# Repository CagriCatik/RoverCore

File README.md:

# RoverCore

Modulare VCU-Trägerplatine (Rev 1) für einen RC-Rover: steckbares
ESP32-S3-DevKitC-1, IMU (Adafruit 4438), OLED (Adafruit 326), geregelte
Servoschiene, 5-V-Logikversorgung, LED-, Empfänger- und UART-Ausgänge.
KiCad 10.0.7, 4 Lagen, 160 × 85 mm (Variante B, vier M3-Eckbohrungen).

**Stand 2026-11-18: Variante B umgesetzt, DRAFT-Paket A3 (NO-GO). Fertigung gestoppt bis zum Fahrzeugabgleich.**
ERC, DRC und Schaltplan-Parität bestehen im lokalen Lauf. Der
JLCPCB-Regelsatz im DRC prüft Kupfer, Bohrungen und Texte, aber keine
Linienbreiten im Bestückungsdruck (bekannte Abweichung, siehe unten). Das ist ein Werkzeugergebnis; elektrische, thermische und
fertigungstechnische Freigabe stehen aus. Nächster Schritt ist der
prüfbare Prototyp nach dem [Inbetriebnahmeplan](docs/bringup.md).

## Ansichten

Review-Ansichten (`hardware/scripts/render_populated_review.py`): Bauteile mit
KiCad-Bibliotheksmodell erscheinen normal. J102/J103 zeigen das Molex-Herstellermodell
(projektlokal, nicht in Git). J101 XT30, BZ101, Q101, Q401/Q402 und D601–D604, D606–D608 zeigen **selbst erzeugte,
vereinfachte Gehäusemodelle nach den Maßzeichnungen der Hersteller** – keine heruntergeladenen Herstellermodelle
(`hardware/scripts/make_package_models.py`, MIT, als STEP und VRML; Maße und Quellen in
`hardware/libraries/3d-models/models.csv`; geschätzt bzw. vereinfacht: XT30-Höhe, Anschlussform BZ101).
**Blau** sind Hüllkörper der gesteckten Module (DevKit, OLED, IMU), Höhen geschätzt. Hüllkörper und eigene Modelle
sind keine verlässlichen mechanischen Modelle; die echten Teile entscheiden beim Passungstest.
Status je Position in `qa/generated/populated/model_status.csv`, Bericht 3g, 3l, 3m.

| Mit Modulen | Ohne Module (Buchsenleisten) |
|---|---|
|  |  |
|  |  |
|  |  |
|  |  |

Befestigung Variante B ([Bericht](docs/vcu/rev1-befestigung-vorschlag.md)): vier M3-Bohrungen, NPTH 3,2 mm,
(4,5 | 4,5), (4,5 | 80,5), (155,5 | 18,0), (155,5 | 80,5); vorläufig bis zum Fahrzeugabgleich; orange in
den 3D-Ansichten = Hüllkörper für Scheibe, Kopf und 10-mm-Abstandshalter.

**Im Browser ansehen:** [drehbares 3D-Modell und interaktive Stückliste (iBOM)](https://cagricatik.github.io/RoverCore/vcu/ansicht/)
(DRAFT A3.1; ohne die Herstellermodelle von J102/J103, siehe dort).

Aus den exportierten Gerber- und Bohrdateien gezeichnet
(`scripts/kit fab preview`), also so, wie der Fertiger sie erhält:

| Oberseite (Gerber) | Unterseite (Gerber, von unten) | Innenlage In1 (GND) |
|---|---|---|
|  |  |  |

## Eckdaten (Auslegung, nicht gemessen)

| Größe | Wert |
|---|---|
| Eingang | 3S-LiPo, 9,0–12,6 V, XT30, Sicherung 15 A, Verpolschutz Q101, TVS D101 |
| Servoschiene | LTC7803, Sollwert 6,8 V (vorläufig, O-19), Auslegung 11,2 A (zwei blockierte Lenkservos), Strommessung INA240A3 an 2 mΩ |
| Logik | TPS54302, +5V 4,74–5,16 V; DevKit über D501 (PMEG4010CEH), +3V3 aus dem DevKit-LDO |
| Freigabe | `SERVO_PWR_EN` und Freigabe-Latch (SW501, Wiederanlaufsperre 9,62–10,40 V) |
| Lagenaufbau | Fertigungsvorgabe 35 / 17,5 / 17,5 / 35 µm, Prepreg 0,1 mm, 1,6 mm, Hülse IPC-6012 Kl. 2 – beim Fertiger zu bestätigen |

## Dokumentation

| Dokument | Inhalt |
|---|---|
| [Erstinbetriebnahme](docs/bringup.md) | Schrittfolge Versorgung, D501, Servostrompfad, Grenzwerte und Abbruchkriterien |
| [Versorgung und Boardwahl](docs/vcu/rev1-versorgung-und-boardwahl.md) | Auslegung aller Versorgungen, Schutz, Wiederanlaufsperre |
| [Pin- und Anschlussplan](docs/vcu/rev1-pin-und-anschlussplan.md) | GPIO-Belegung, Stecker (maschinenlesbar: `hardware/interfaces/pinmap.csv`) |
| [Platzierung, Routing, Fertigung](docs/vcu/rev1-platzierung.md) | Platzierung, Routing K1, Strompfade (3j), Fertigerabgleich und DRAFT-Paket (3k) |
| [Mechanischer Abgleich](docs/vcu/rev1-mechanik-abgleich.md) | Prüfliste am Fahrzeug, 1:1-Vorlage, Auflage unter dem DevKit |
| [Review 2026-11-15](docs/vcu/rev1-review-2026-11-15.md) · [Werkzeuge](docs/vcu/tooling-integration.md) | Schaltplan-Review, lokale Werkzeuge |
| [Engineering-Richtlinien](docs/engineering/README.md) | allgemeine Regeln aus dem Template |

Online: <https://cagricatik.github.io/RoverCore/>

## Offen vor einer Bestellung

- Lagenaufbau und **Mindest**-Hülsendicke 18 µm schriftlich beim Fertiger
  bestellen (JLCPCB nennt nur einen Mittelwert von 18 µm).
- D502 festgelegt (Würth 150060RS75000); LCSC-Nummer und JLCPCB-Bestand prüfen.
- Datenblattfelder (44 Teile), 3D-Modelle (14), Bauteilakten.
- Bestückungsdruck: 1 211 Umrissstriche mit 0,12 mm im exportierten Gerber
  (JLCPCB verlangt 0,15 mm); Entscheidung offen (Bericht 3l).
- **Befestigung Variante B umgesetzt** (Kontur 160 × 85, vier Eckbohrungen); offen ist der
  Abgleich am Fahrzeug mit der 1:1-Vorlage ([Prüfliste](docs/vcu/rev1-mechanik-abgleich.md)) und der
  Stecktest am DevKit (ob die Auflage unter dem DevKit nötig ist). Ergebnisse der Prüfung des Umbaus
  in [rev1-befestigung-vorschlag.md](docs/vcu/rev1-befestigung-vorschlag.md).
- Bohrdateien: `kit export` liefert getrennt `RoverCore-PTH.drl` und
  `RoverCore-NPTH.drl`; beide hochladen und die 10 NPTH-Löcher in der
  Fertiger-Vorschau prüfen (Bericht 3n).
- 3D / STEP: Alle Carrier-Teile haben ein Modell (`models_3d` 0 Funde). Der Board-STEP (`kit export`,
  `mechanical/board.step`) enthält die eigenen Modelle, ist für Gehäusekonstruktion und Kollisionsprüfung aber
  **unvollständig**: Die gesteckten Module DevKit, OLED und IMU fehlen darin (nur ihre Buchsenleisten; die blauen
  Hüllen gibt es nur in den Review-Bildern), und das Molex-Modell J102/J103 fehlt in einem frischen Checkout,
  solange `vendor/` nicht geladen ist. Eigene Modelle sind vereinfacht (XT30-Höhe geschätzt).
- GO-Freigabe nur mit signierter Freigabe (`manufacturing/approval.example.json`)
  und `--authorize`.

## Repository

| Pfad | Inhalt |
| --- | --- |
| `RoverCore.kicad_pro/.kicad_sch/.kicad_pcb/.kicad_dru` | KiCad-Projekt (Hardware-Wahrheit), Fertiger-Regelsatz |
| `hardware/` | Eigene Bibliotheken (`${KIPRJMOD}`), Schnittstellen, Simulation, Board-Skripte |
| `firmware/` | Firmware, BSP und Treiber (optional) |
| `components/` | Bauteilakten, Datenblätter, SPICE-Modelle |
| `manufacturing/` | Freigabe-Checkliste, Freigaben, erzeugte Exporte (nicht versioniert) |
| `docs/` | Anforderungen, Architektur, Schnittstellen, Inbetriebnahme, Berichte |
| `qa/` | Prüfkonfiguration, Reviews, Berichte |

## Befehle

```sh
scripts/kit install                       # einmalig: lokale .venv (kicad-python, numpy, scipy)
scripts/kit doctor                        # Umgebungsdiagnose, nur lesend
scripts/kit verify .                      # ERC, DRC, Parität, Bibliotheken, Metadaten, 3D, BOM
scripts/kit export . --revision A1        # DRAFT-Fertigungspaket (NO-GO)
scripts/kit thermal analyze .             # stationäre Thermik-Schätzung
scripts/kit power paths .                 # Gleichstrom-Pfade im Kupfer (Schätzung), Fälle in current-paths.json
```

Prüfwerkzeuge für Layout und Fertigungspaket (nur lesend, Ergebnisse unter `qa/generated/`):

```sh
scripts/kit fab check . manufacturing/releases/generated/rev-A3-DRAFT     # Paket gegen Board
scripts/kit fab preview . manufacturing/releases/generated/rev-A3-DRAFT   # Gerber-/Bohrbilder
scripts/kit board diff ALT.kicad_pcb RoverCore.kicad_pcb --project .      # Kupfer-/Bauteilvergleich
scripts/kit models fit . BZ101 hardware/libraries/3d-models/project/SameSky_CMT-8540S-SMT_8.5x8.5x4.0mm.step  # 3D-Sitz
scripts/kit mounting print . --washer 7 --body J101 --body U501           # 1:1-Bohrbild (allgemein)
```

Die Lastfälle für `power paths` stehen in
[`hardware/simulations/power/current-paths.json`](hardware/simulations/power/current-paths.json),
alle Ströme und die Hülsendicke mit Quelle in
[`hardware/interfaces/assumptions.json`](hardware/interfaces/assumptions.json). Die früheren Skripte
`current_map.py`, `board_copper_diff.py`, `fab_package_check.py`, `gerber_preview.py` und
`model_fit_check.py` (in älteren Berichtsabschnitten noch genannt) sind durch diese Befehle ersetzt und
nur noch in der Git-Historie (bis `53f6d7f`). Die RoverCore-spezifischen Montagebilder
(`render_mounting_print.py` mit SUPPORT-Zone und Steckrichtungen, `render_mounting_drawing.py`,
`render_mounting_proposal.py`) bleiben in `hardware/scripts`.

Die Werkzeuge sind aus PCB-Project-Template 2.0.0 übernommen; Herkunft,
Lizenz und lokale Änderungen stehen in [`tools/VENDORED.md`](tools/VENDORED.md).
Regeln für automatisierte Änderungen: [`AGENTS.md`](AGENTS.md).

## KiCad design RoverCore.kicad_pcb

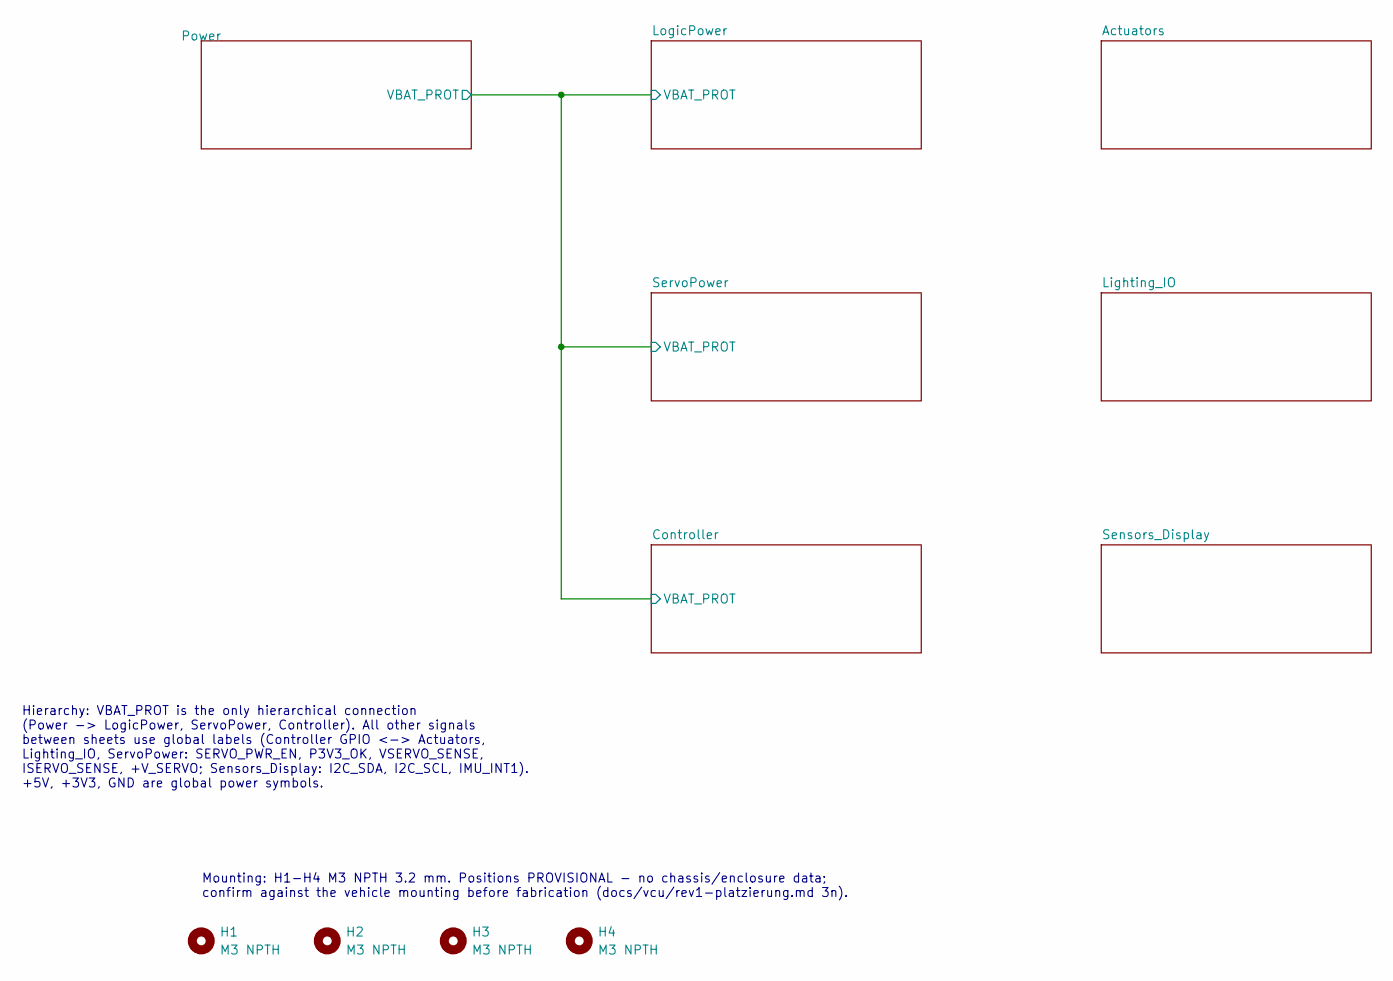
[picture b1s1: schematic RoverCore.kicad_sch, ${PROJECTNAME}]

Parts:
H1, H2, H3, H4: M3 NPTH; MountingHole_3.2mm_M3_NPTH_Keepout

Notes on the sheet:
Hierarchy: VBAT_PROT is the only hierarchical connection (Power -> LogicPower, ServoPower, Controller). All other signals between sheets use global labels (Controller GPIO <-> Actuators, Lighting_IO, ServoPower: SERVO_PWR_EN, P3V3_OK, VSERVO_SENSE, ISERVO_SENSE, +V_SERVO; Sensors_Display: I2C_SDA, 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
Mounting: H1-H4 M3 NPTH 3.2 mm. Positions PROVISIONAL - no chassis/enclosure data; confirm against the vehicle mounting before fabrication (docs/vcu/rev1-platzierung.md 3n).

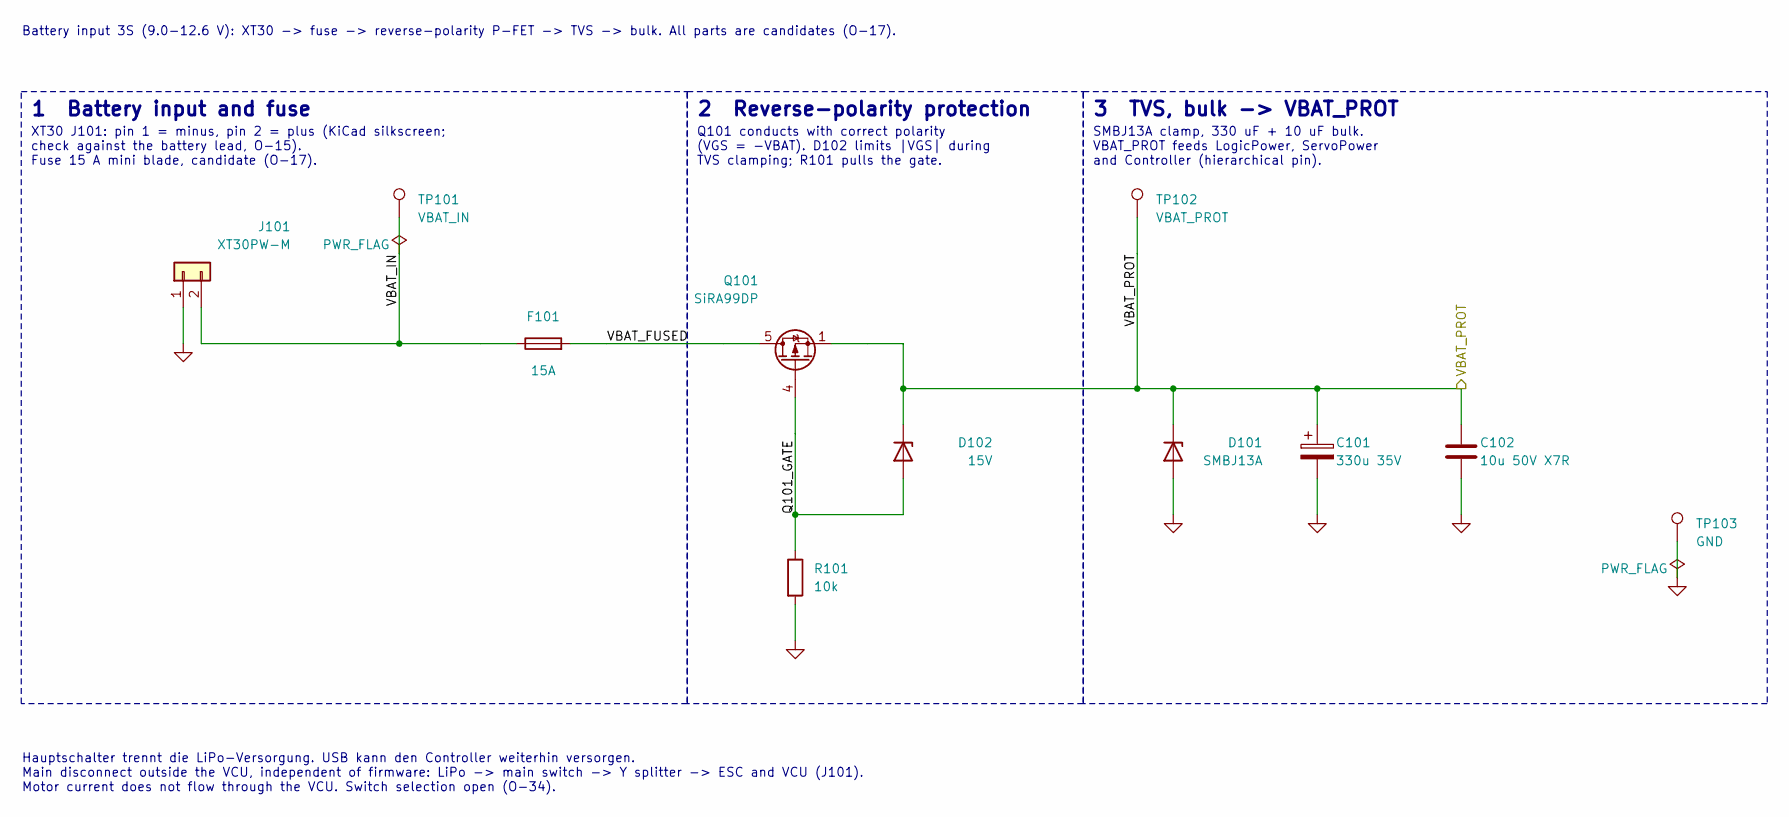
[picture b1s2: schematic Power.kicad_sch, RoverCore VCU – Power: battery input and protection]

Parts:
C101: 330u 35V; CP_Elec_10x10.5; MPN 35PJV330M10X10.5; LCSC C3274921
C102: 10u 50V X7R; C_1210_3225Metric; MPN CL32B106KBJNNNE; LCSC C138687
D101: SMBJ13A; D_SMB; MPN SMBJ13A; LCSC C151252
D102: 15V; D_SOD-123; MPN MMSZ5245BT1G; LCSC C129730
F101: 15A; Fuseholder_Blade_Mini_Keystone_3568; MPN 3568; LCSC C5249699
J101: XT30PW-M; AMASS_XT30PW-M_1x02_P2.50mm_Horizontal; MPN XT30PW-M30.G.Y; LCSC C431092
Q101: SiRA99DP; PowerPAK_SO-8_Single; MPN SiRA99DP-T1-GE3; LCSC C3289459
R101: 10k; R_0603_1608Metric; MPN RC0603FR-0710KL; LCSC C98220
TP101: VBAT_IN; TestPoint_Pad_D1.5mm
TP102: VBAT_PROT; TestPoint_Pad_D1.5mm
TP103: GND; TestPoint_Pad_D1.5mm

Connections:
/Power/Q101_GATE: D102.2 (A), Q101.4 (G), R101.1
/Power/VBAT_FUSED: F101.2, Q101.5 (D)
/Power/VBAT_IN: F101.1, J101.2, TP101.1
/Power/VBAT_PROT: C101.1, C102.1, D101.1 (K), D102.1 (K), Q101.1 (S), Q101.2 (S), Q101.3 (S), TP102.1; also elsewhere on the board
GND: C101.2, C102.2, D101.2 (A), J101.1, R101.2, TP103.1; also elsewhere on the board

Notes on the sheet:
1 Battery input and fuse
XT30 J101: pin 1 = minus, pin 2 = plus (KiCad silkscreen; check against the battery lead, O-15). Fuse 15 A mini blade, candidate (O-17).
2 Reverse-polarity protection
Q101 conducts with correct polarity (VGS = -VBAT). D102 limits |VGS| during TVS clamping; R101 pulls the gate.
3 TVS, bulk -> VBAT_PROT
SMBJ13A clamp, 330 uF + 10 uF bulk. VBAT_PROT feeds LogicPower, ServoPower and Controller (hierarchical pin).
Battery input 3S (9.0-12.6 V): XT30 -> fuse -> reverse-polarity P-FET -> TVS -> bulk. All parts are candidates (O-17).
Hauptschalter trennt die LiPo-Versorgung. USB kann den Controller weiterhin versorgen. Main disconnect outside the VCU, independent of firmware: LiPo -> main switch -> Y splitter -> ESC and VCU (J101). Motor current does not flow through the VCU. Switch selection open (O-34).

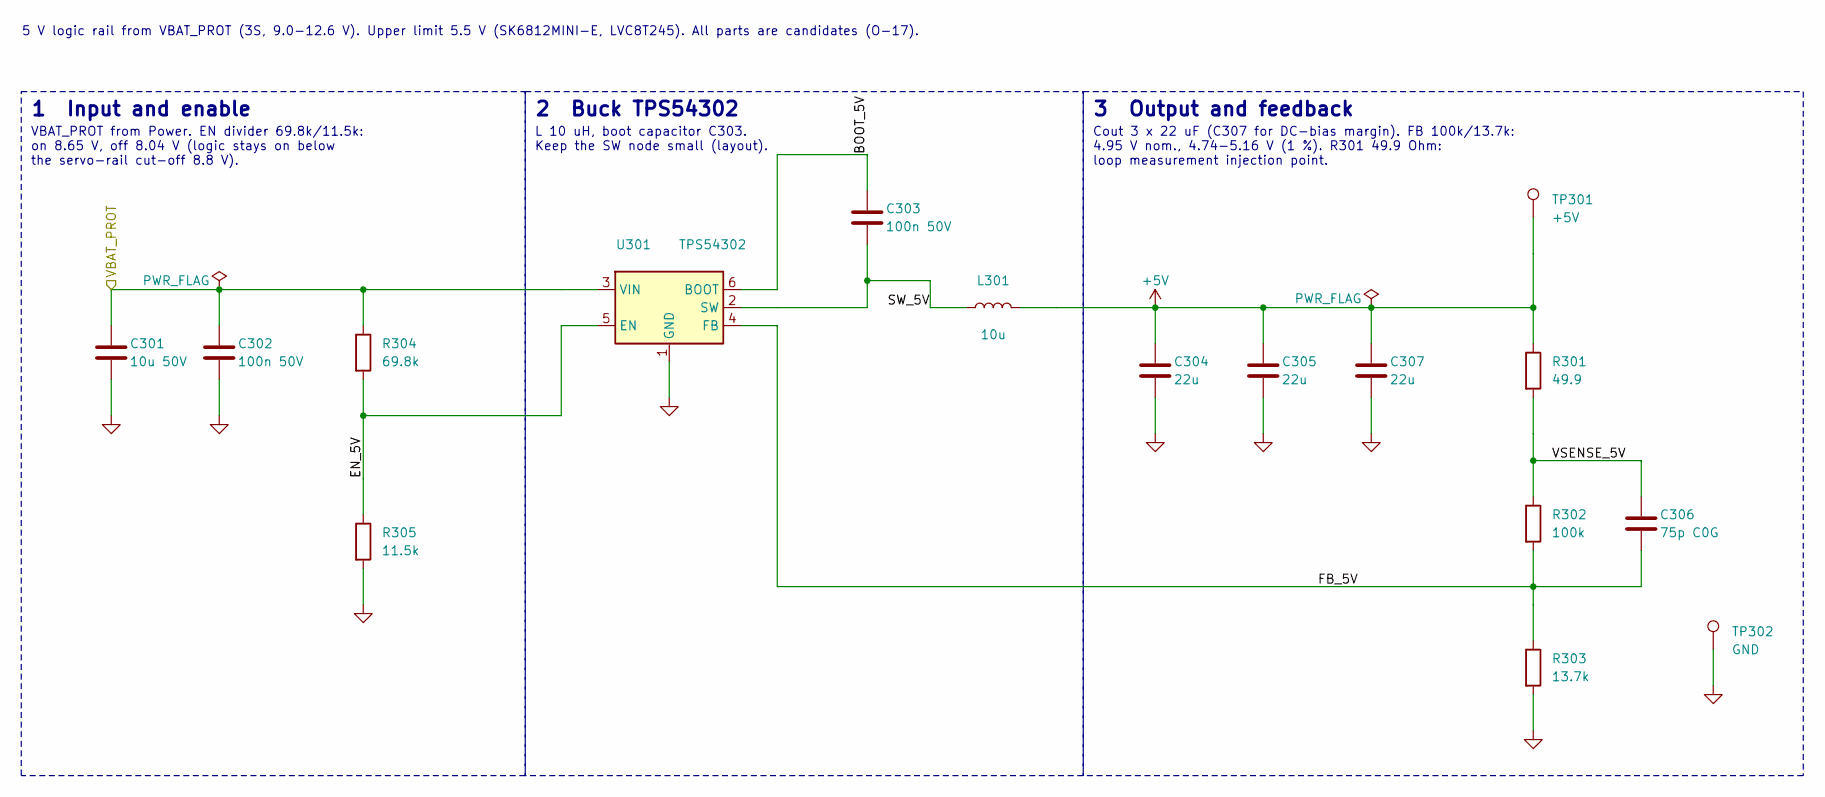
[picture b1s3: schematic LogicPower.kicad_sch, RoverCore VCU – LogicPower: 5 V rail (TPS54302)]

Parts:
C301: 10u 50V; C_1210_3225Metric; MPN CL32B106KBJNNNE; LCSC C138687
C302, C303: 100n 50V; C_0603_1608Metric; MPN CC0603KRX7R9BB104; LCSC C14663
C304, C305, C307: 22u; C_1210_3225Metric; MPN GRM32ER71E226KE15L; LCSC C21397
C306: 75p C0G; C_0603_1608Metric; MPN CC0603JRNPO9BN750; LCSC C282074
L301: 10u; L_Wuerth_XHMI-6060; MPN 74439346100; LCSC C2651185
R301: 49.9; R_0603_1608Metric; MPN RC0603FR-0749R9L; LCSC C114625
R302: 100k; R_0603_1608Metric; MPN RC0603FR-07100KL; LCSC C14675
R303: 13.7k; R_0603_1608Metric; MPN RC0603FR-0713K7L; LCSC C482771
R304: 69.8k; R_0603_1608Metric; MPN RC0603FR-0769K8L; LCSC C137689
R305: 11.5k; R_0603_1608Metric; MPN RC0603FR-0711K5L; LCSC C137802
TP301: +5V; TestPoint_Pad_D1.5mm
TP302: GND; TestPoint_Pad_D1.5mm
U301: TPS54302; TSOT-23-6; MPN TPS54302DDCR; LCSC C311983

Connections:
+5V: C304.1, C305.1, C307.1, L301.2, R301.1, TP301.1; also elsewhere on the board
/LogicPower/BOOT_5V: C303.1, U301.6 (BOOT)
/LogicPower/EN_5V: R304.2, R305.1, U301.5 (EN)
/LogicPower/FB_5V: C306.2, R302.2, R303.1, U301.4 (FB)
/LogicPower/SW_5V: C303.2, L301.1, U301.2 (SW)
/LogicPower/VSENSE_5V: C306.1, R301.2, R302.1
/Power/VBAT_PROT: C301.1, C302.1, R304.1, U301.3 (VIN); also elsewhere on the board
GND: C301.2, C302.2, C304.2, C305.2, C307.2, R303.2, R305.2, TP302.1, U301.1 (GND); also elsewhere on the board

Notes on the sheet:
1 Input and enable
VBAT_PROT from Power. EN divider 69.8k/11.5k: on 8.65 V, off 8.04 V (logic stays on below the servo-rail cut-off 8.8 V).
2 Buck TPS54302
L 10 uH, boot capacitor C303. Keep the SW node small (layout).
3 Output and feedback
Cout 3 x 22 uF (C307 for DC-bias margin). FB 100k/13.7k: 4.95 V nom., 4.74-5.16 V (1 %). R301 49.9 Ohm: loop measurement injection point.
5 V logic rail from VBAT_PROT (3S, 9.0-12.6 V). Upper limit 5.5 V (SK6812MINI-E, LVC8T245). All parts are candidates (O-17).

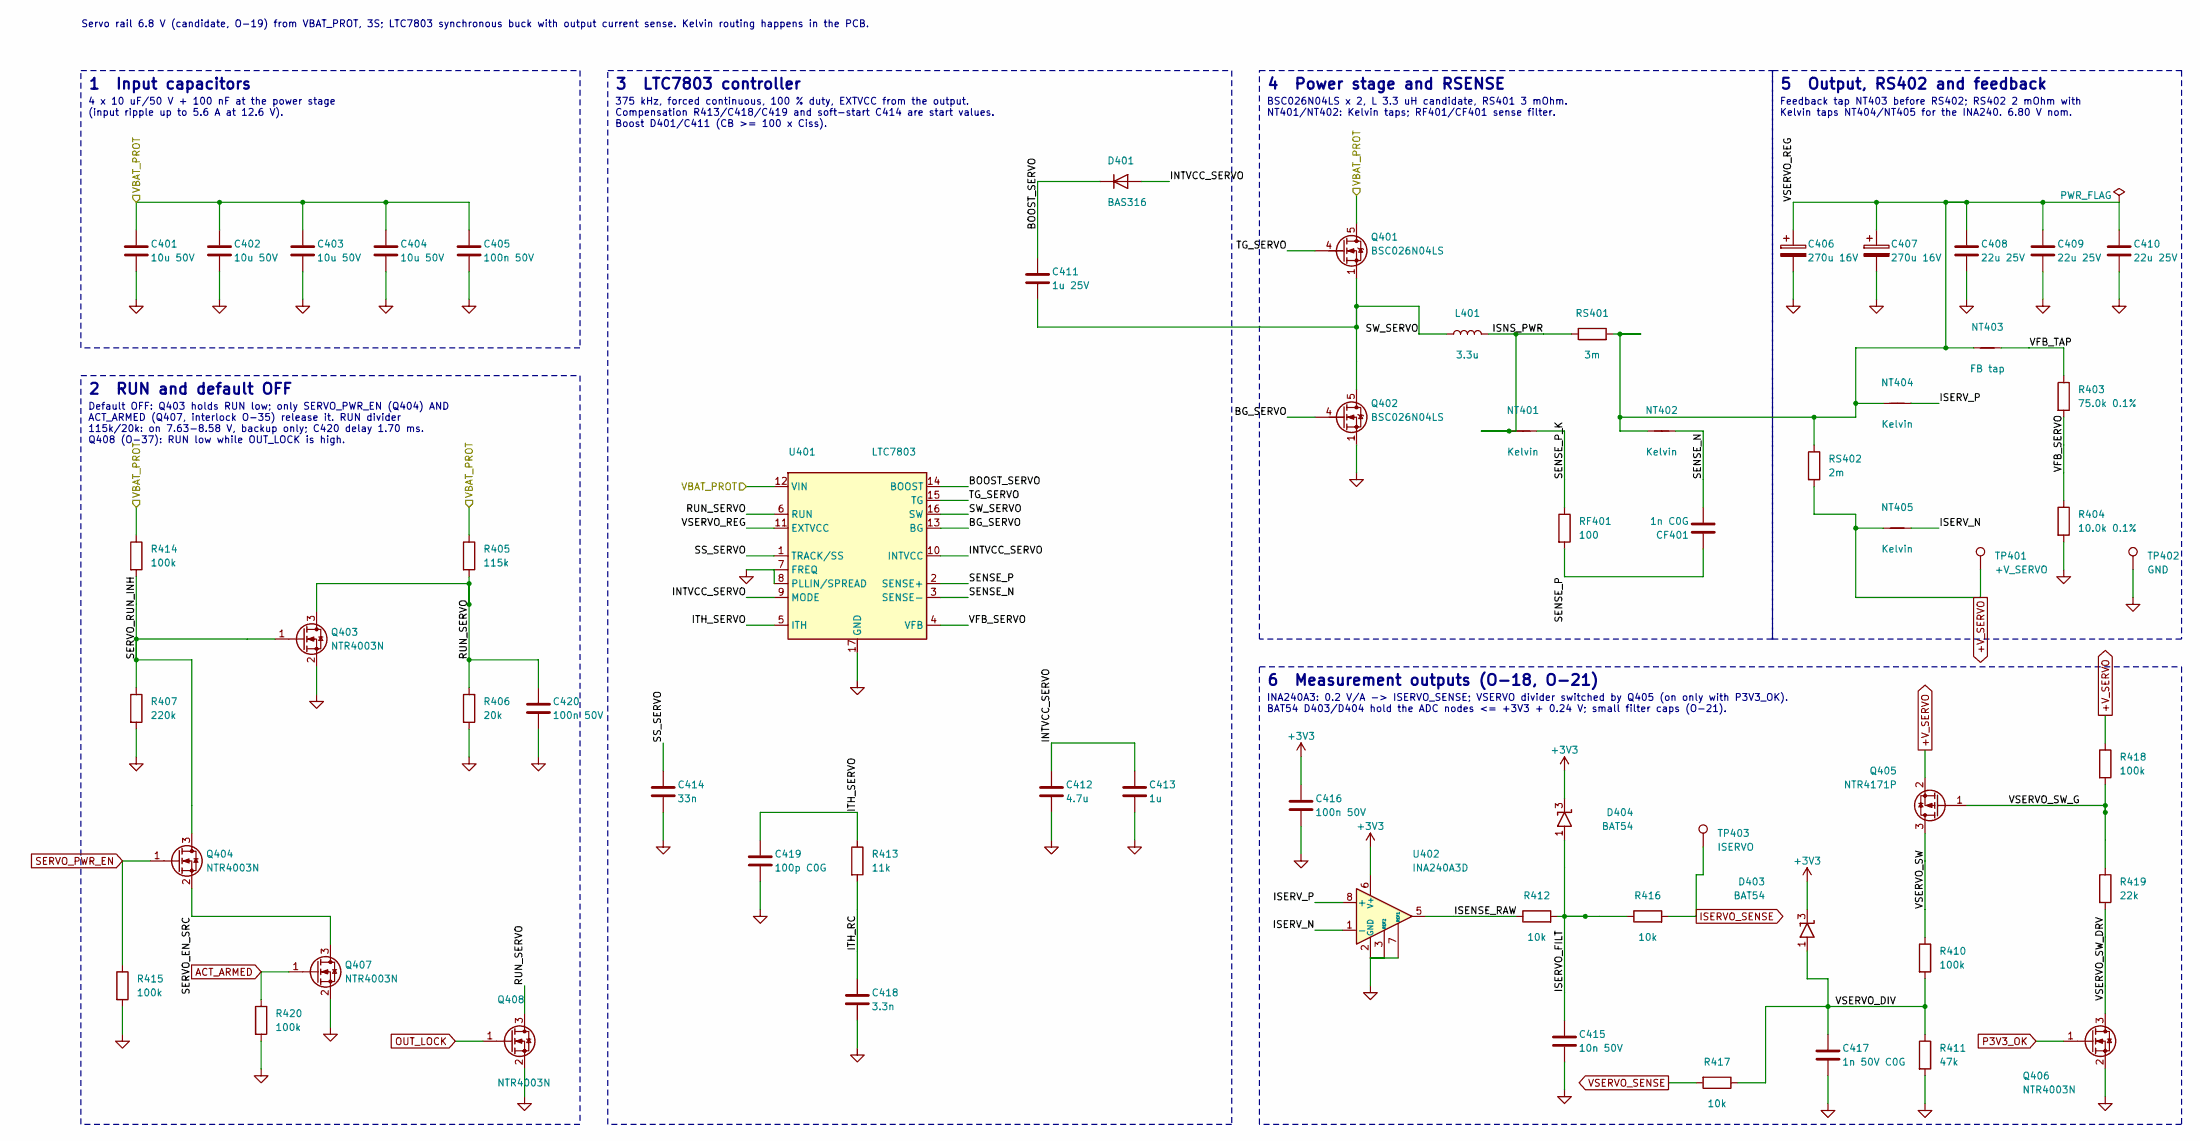
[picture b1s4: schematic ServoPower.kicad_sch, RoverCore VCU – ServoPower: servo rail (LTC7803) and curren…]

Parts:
C401, C402, C403, C404: 10u 50V; C_1210_3225Metric; MPN CL32B106KBJNNNE; LCSC C138687
C405, C416, C420: 100n 50V; C_0603_1608Metric; MPN CC0603KRX7R9BB104; LCSC C14663
C406, C407: 270u 16V; CP_Panasonic_OSCON_SVPG_C8; MPN 16SVPG270MX; LCSC C2161621
C408, C409, C410: 22u 25V; C_1210_3225Metric; MPN GRM32ER71E226KE15L; LCSC C21397
C411: 1u 25V; C_0603_1608Metric; MPN CL10B105KA8NNNC; LCSC C29936
C412: 4.7u; C_0805_2012Metric; MPN CC0805KKX7R8BB475; LCSC C354262
C413: 1u; C_0603_1608Metric; MPN CL10B105KA8NNNC; LCSC C29936
C414: 33n; C_0603_1608Metric; MPN CL10B333KB8NNNC; LCSC C21117
C415: 10n 50V; C_0603_1608Metric; MPN CC0603KRX7R9BB103; LCSC C100042
C417: 1n 50V C0G; C_0603_1608Metric; MPN CC0603JRNPO9BN102; LCSC C106246
C418: 3.3n; C_0603_1608Metric; MPN CC0603JRNPO9BN332; LCSC C107048
C419: 100p C0G; C_0603_1608Metric; MPN CL10C101JB8NNNC; LCSC C14858
CF401: 1n C0G; C_0603_1608Metric; MPN CC0603JRNPO9BN102; LCSC C106246
D401: BAS316; D_SOD-323; MPN BAS316,115; LCSC C109218
D403, D404: BAT54; SOT-23; MPN BAT54,215; LCSC C85084
L401: 3.3u; L_Coilcraft_XAL1010-XXX; MPN XAL1010-332MED; LCSC C3911672
NT401, NT402, NT404, NT405: Kelvin; NetTie-2_SMD_Pad0.5mm
NT403: FB tap; NetTie-2_SMD_Pad0.5mm
Q401, Q402: BSC026N04LS; Infineon_PG-TDSON-8_BSC026N04LS; MPN BSC026N04LS; LCSC C3039672
Q403, Q404, Q406, Q407, Q408: NTR4003N; SOT-23; MPN NTR4003NT1G; LCSC C82325
Q405: NTR4171P; SOT-23; MPN NTR4171PT1G; LCSC C146715
R403: 75.0k 0.1%; R_0603_1608Metric; MPN RT0603BRD0775KL; LCSC C723587
R404: 10.0k 0.1%; R_0603_1608Metric; MPN RT0603BRD0710KL; LCSC C95204
R405: 115k; R_0603_1608Metric; MPN RC0603FR-07115KL
R406: 20k; R_0603_1608Metric; MPN RC0603FR-0720KL; LCSC C105575
R407: 220k; R_0603_1608Metric; MPN RC0603FR-07220KL; LCSC C123420
R410, R414, R415, R418, R420: 100k; R_0603_1608Metric; MPN RC0603FR-07100KL; LCSC C14675
R411: 47k; R_0603_1608Metric; MPN RC0603FR-0747KL; LCSC C105579
R412, R416, R417: 10k; R_0603_1608Metric; MPN RC0603FR-0710KL; LCSC C98220
R413: 11k; R_0603_1608Metric; MPN RC0603FR-0711KL; LCSC C137801
R419: 22k; R_0603_1608Metric; MPN RC0603FR-0722KL; LCSC C114065
RF401: 100; R_0603_1608Metric; MPN RC0603FR-07100RL; LCSC open (O-22)
RS401: 3m; R_Vishay_WSL1020; MPN WSL10203L000FEA; LCSC C844481
RS402: 2m; R_Vishay_WSL1020; MPN WSL10202L000FEA; LCSC C1711510
TP401: +V_SERVO; TestPoint_Pad_D1.5mm
TP402: GND; TestPoint_Pad_D1.5mm
TP403: ISERVO; TestPoint_Pad_D1.5mm
U401: LTC7803; ADI_MSE16_MSOP-16-1EP_ThermalVias; MPN LTC7803EMSE#PBF; LCSC C1016554
U402: INA240A3D; SOIC-8_3.9x4.9mm_P1.27mm; MPN INA240A3DR; LCSC C2060584

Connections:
+3V3: C416.1, D403.3 (K), D404.3 (K), U402.6 (V+); also elsewhere on the board
+V_SERVO: NT405.1, Q405.2 (S), R418.1, RS402.2, TP401.1; also elsewhere on the board
/Power/VBAT_PROT: C401.1, C402.1, C403.1, C404.1, C405.1, Q401.5 (D), R405.1, R414.1, U401.12 (VIN); also elsewhere on the board
/ServoPower/BG_SERVO: Q402.4 (G), U401.13 (BG)
/ServoPower/BOOST_SERVO: C411.1, D401.1 (K), U401.14 (BOOST)
/ServoPower/INTVCC_SERVO: C412.1, C413.1, D401.2 (A), U401.9 (MODE), U401.10 (INTVCC)
/ServoPower/ISENSE_RAW: R412.1, U402.5
/ServoPower/ISERVO_FILT: C415.1, D404.1 (A), R412.2, R416.1
/ServoPower/ISERV_N: NT405.2, U402.1 (-)
/ServoPower/ISERV_P: NT404.2, U402.8 (+)
/ServoPower/ISNS_PWR: L401.2, NT401.1, RS401.1
/ServoPower/ITH_RC: C418.1, R413.2
/ServoPower/ITH_SERVO: C419.1, R413.1, U401.5 (ITH)
/ServoPower/RUN_SERVO: C420.1, Q403.3 (D), Q408.3 (D), R405.2, R406.1, U401.6 (RUN)
/ServoPower/SENSE_N: CF401.2, NT402.2, U401.3 (SENSE-)
/ServoPower/SENSE_P: CF401.1, RF401.2, U401.2 (SENSE+)
/ServoPower/SENSE_P_K: NT401.2, RF401.1
/ServoPower/SERVO_EN_SRC: Q404.2 (S), Q407.3 (D)
/ServoPower/SERVO_RUN_INH: Q403.1 (G), Q404.3 (D), R407.1, R414.2
/ServoPower/SS_SERVO: C414.1, U401.1 (TRACK/SS)
/ServoPower/SW_SERVO: C411.2, L401.1, Q401.1 (S), Q401.2 (S), Q401.3 (S), Q402.5 (D), U401.16 (SW)
/ServoPower/TG_SERVO: Q401.4 (G), U401.15 (TG)
/ServoPower/VFB_SERVO: R403.2, R404.1, U401.4 (VFB)
/ServoPower/VFB_TAP: NT403.2, R403.1
/ServoPower/VSERVO_DIV: C417.1, D403.1 (A), R410.2, R411.1, R417.1
/ServoPower/VSERVO_REG: C406.1, C407.1, C408.1, C409.1, C410.1, NT402.1, NT403.1, NT404.1, RS401.2, RS402.1, U401.11 (EXTVCC)
/ServoPower/VSERVO_SW: Q405.3 (D), R410.1
/ServoPower/VSERVO_SW_DRV: Q406.3 (D), R419.2
/ServoPower/VSERVO_SW_G: Q405.1 (G), R418.2, R419.1
ACT_ARMED: Q407.1 (G), R420.1; also elsewhere on the board
GND: C401.2, C402.2, C403.2, C404.2, C405.2, C406.2, C407.2, C408.2, C409.2, C410.2, C412.2, C413.2, C414.2, C415.2, C416.2, C417.2, C418.2, C419.2, C420.2, Q402.1 (S), Q402.2 (S), Q402.3 (S), Q403.2 (S), Q406.2 (S), Q407.2 (S), Q408.2 (S), R404.2, R406.2, R407.2, R411.2, R415.2, R420.2, TP402.1, U401.7 (FREQ), U401.8 (PLLIN/SPREAD), U401.17 (GND), U402.2 (GND), U402.3 (REF2), U402.4 (GND), U402.7 (REF1); also elsewhere on the board
ISERVO_SENSE: R416.2, TP403.1; also elsewhere on the board
OUT_LOCK: Q408.1 (G); also elsewhere on the board
P3V3_OK: Q406.1 (G); also elsewhere on the board
SERVO_PWR_EN: Q404.1 (G), R415.1; also elsewhere on the board
VSERVO_SENSE: R417.2; also elsewhere on the board

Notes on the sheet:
1 Input capacitors
4 x 10 uF/50 V + 100 nF at the power stage (input ripple up to 5.6 A at 12.6 V).
2 RUN and default OFF
Default OFF: Q403 holds RUN low; only SERVO_PWR_EN (Q404) AND ACT_ARMED (Q407, interlock O-35) release it. RUN divider 115k/20k: on 7.63-8.58 V, backup only; C420 delay 1.70 ms. Q408 (O-37): RUN low while OUT_LOCK is high.
3 LTC7803 controller
375 kHz, forced continuous, 100 % duty, EXTVCC from the output. Compensation R413/C418/C419 and soft-start C414 are start values. Boost D401/C411 (CB >= 100 x Ciss).
4 Power stage and RSENSE
BSC026N04LS x 2, L 3.3 uH candidate, RS401 3 mOhm. NT401/NT402: Kelvin taps; RF401/CF401 sense filter.
5 Output, RS402 and feedback
Feedback tap NT403 before RS402; RS402 2 mOhm with Kelvin taps NT404/NT405 for the INA240. 6.80 V nom.
6 Measurement outputs (O-18, O-21)
INA240A3: 0.2 V/A -> ISERVO_SENSE; VSERVO divider switched by Q405 (on only with P3V3_OK). BAT54 D403/D404 hold the ADC nodes <= +3V3 + 0.24 V; small filter caps (O-21).
Servo rail 6.8 V (candidate, O-19) from VBAT_PROT, 3S; LTC7803 synchronous buck with output current sense. Kelvin routing happens in the PCB.

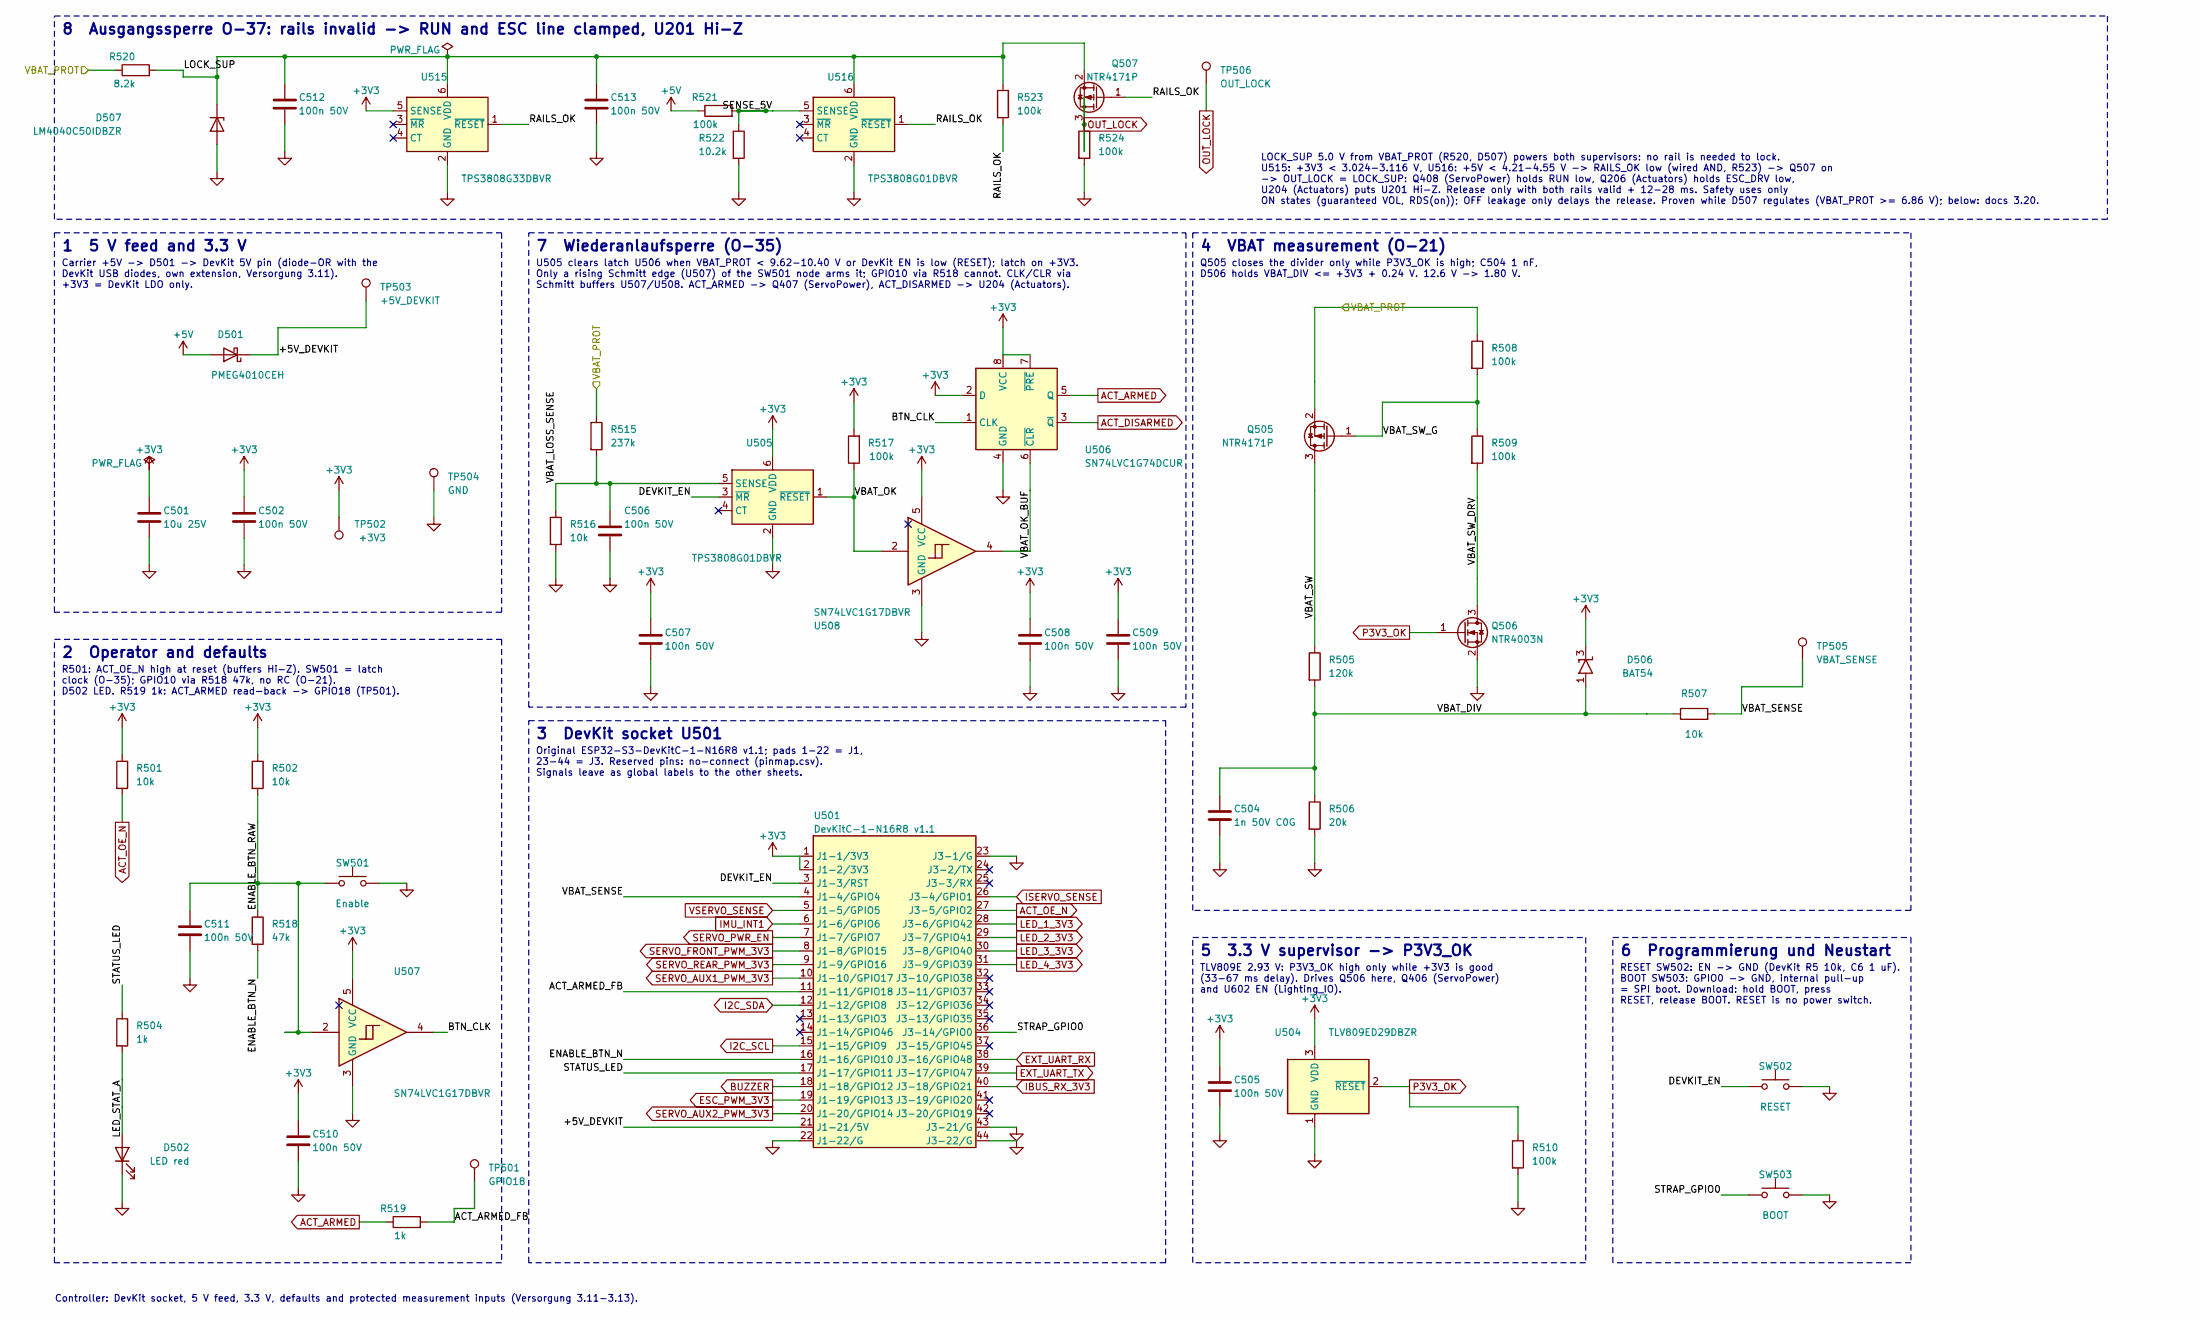
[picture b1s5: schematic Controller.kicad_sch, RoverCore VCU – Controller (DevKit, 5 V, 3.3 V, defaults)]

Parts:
C501: 10u 25V; C_0805_2012Metric; MPN CL21A106KAYNNNE; LCSC C15850
C502, C505, C506, C507, C508, C509, C510, C511, C512, C513: 100n 50V; C_0603_1608Metric; MPN CC0603KRX7R9BB104; LCSC C14663
C504: 1n 50V C0G; C_0603_1608Metric; MPN CC0603JRNPO9BN102; LCSC C106246
D501: PMEG4010CEH; D_SOD-123F; MPN PMEG4010CEH,115; LCSC C193342
D502: LED red; LED_0603_1608Metric; MPN 150060RS75000
D506: BAT54; SOT-23; MPN BAT54,215; LCSC C85084
D507: LM4040C50IDBZR; SOT-23; MPN LM4040C50IDBZR; LCSC C69316
Q505, Q507: NTR4171P; SOT-23; MPN NTR4171PT1G; LCSC C146715
Q506: NTR4003N; SOT-23; MPN NTR4003NT1G; LCSC C82325
R501, R502, R507, R516: 10k; R_0603_1608Metric; MPN RC0603FR-0710KL; LCSC C98220
R504, R519: 1k; R_0603_1608Metric; MPN RC0603FR-071KL; LCSC C22548
R505: 120k; R_0603_1608Metric; MPN RC0603FR-07120KL; LCSC C114607
R506: 20k; R_0603_1608Metric; MPN RC0603FR-0720KL; LCSC C105575
R508, R509, R510, R517, R521, R523, R524: 100k; R_0603_1608Metric; MPN RC0603FR-07100KL; LCSC C14675
R515: 237k; R_0603_1608Metric; MPN RC0603FR-07237KL
R518: 47k; R_0603_1608Metric; MPN RC0603FR-0747KL
R520: 8.2k; R_0603_1608Metric; MPN RC0603FR-078K2L; LCSC C114637
R522: 10.2k; R_0603_1608Metric; MPN RC0603FR-0710K2L; LCSC C183219
SW501: Enable; SW_SPST_TL3342; MPN TL3342F160QG; LCSC C2886898
SW502: RESET; SW_SPST_TL3342; MPN TL3342F160QG; LCSC C2886898
SW503: BOOT; SW_SPST_TL3342; MPN TL3342F160QG; LCSC C2886898
TP501: GPIO18; TestPoint_Pad_D1.5mm
TP502: +3V3; TestPoint_Pad_D1.5mm
TP503: +5V_DEVKIT; TestPoint_Pad_D1.5mm
TP504: GND; TestPoint_Pad_D1.5mm
TP505: VBAT_SENSE; TestPoint_Pad_D1.5mm
TP506: OUT_LOCK; TestPoint_Pad_D1.5mm
U501: DevKitC-1-N16R8 v1.1; ESP32-S3-DevKitC-1_v1.1_Socket_2x1x22_P2.54mm; MPN ESP32-S3-DevKitC-1-N16R8 (v1.1, origina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
U504: TLV809ED29DBZR; SOT-23; MPN TLV809ED29DBZR; LCSC C2864833
U505: TPS3808G01DBVR; SOT-23-6; MPN TPS3808G01DBVR
U506: SN74LVC1G74DCUR; VSSOP-8_2.3x2mm_P0.5mm; MPN SN74LVC1G74DCUR
U507, U508: SN74LVC1G17DBVR; SOT-23-5; MPN SN74LVC1G17DBVR
U515: TPS3808G33DBVR; SOT-23-6; MPN TPS3808G33DBVR; LCSC C43698
U516: TPS3808G01DBVR; SOT-23-6; MPN TPS3808G01DBVR; LCSC C19653

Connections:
+3V3: C501.1, C502.1, C505.1, C507.1, C508.1, C509.1, C510.1, D506.3 (K), R501.1, R502.1, R517.2, TP502.1, U501.1 (J1-1/3V3), U501.2 (J1-2/3V3), U504.3 (VDD), U505.6 (VDD), U506.2 (D), U506.7 (~PRE), U506.8 (VCC), U507.5 (VCC), U508.5 (VCC), U515.5 (SENSE); also elsewhere on the board
+5V: D501.2 (A), R521.1; also elsewhere on the board
/Controller/+5V_DEVKIT: D501.1 (K), TP503.1, U501.21 (J1-21/5V)
/Controller/ACT_ARMED_FB: R519.2, TP501.1, U501.11 (J1-11/GPIO18)
/Controller/BTN_CLK: U506.1 (CLK), U507.4
/Controller/DEVKIT_EN: SW502.1, U501.3 (J1-3/RST), U505.3 (~MR)
/Controller/ENABLE_BTN_N: R518.2, U501.16 (J1-16/GPIO10)
/Controller/ENABLE_BTN_RAW: C511.1, R502.2, R518.1, SW501.1, U507.2
/Controller/LED_STAT_A: D502.2 (A), R504.2
/Controller/LOCK_SUP: C512.1, C513.1, D507.1 (K), Q507.2 (S), R520.2, R523.1, U515.6 (VDD), U516.6 (VDD)
/Controller/RAILS_OK: Q507.1 (G), R523.2, U515.1 (~RESET), U516.1 (~RESET)
/Controller/SENSE_5V: R521.2, R522.1, U516.5 (SENSE)
/Controller/STATUS_LED: R504.1, U501.17 (J1-17/GPIO11)
/Controller/STRAP_GPIO0: SW503.1, U501.36 (J3-14/GPIO0)
/Controller/VBAT_DIV: C504.1, D506.1 (A), R505.2, R506.1, R507.1
/Controller/VBAT_LOSS_SENSE: C506.1, R515.2, R516.1, U505.5 (SENSE)
/Controller/VBAT_OK: R517.1, U505.1 (~RESET), U508.2
/Controller/VBAT_OK_BUF: U506.6 (~CLR), U508.4
/Controller/VBAT_SENSE: R507.2, TP505.1, U501.4 (J1-4/GPIO4)
/Controller/VBAT_SW: Q505.3 (D), R505.1
/Controller/VBAT_SW_DRV: Q506.3 (D), R509.2
/Controller/VBAT_SW_G: Q505.1 (G), R508.2, R509.1
/Power/VBAT_PROT: Q505.2 (S), R508.1, R515.1, R520.1; also elsewhere on the board
ACT_ARMED: R519.1, U506.5 (Q); also elsewhere on the board
ACT_DISARMED: U506.3 (~Q); also elsewhere on the board
ACT_OE_N: R501.2, U501.27 (J3-5/GPIO2); also elsewhere on the board
BUZZER: U501.18 (J1-18/GPIO12); also elsewhere on the board
ESC_PWM_3V3: U501.19 (J1-19/GPIO13); also elsewhere on the board
EXT_UART_RX: U501.38 (J3-16/GPIO48); also elsewhere on the board
EXT_UART_TX: U501.39 (J3-17/GPIO47); also elsewhere on the board
GND: C501.2, C502.2, C504.2, C505.2, C506.2, C507.2, C508.2, C509.2, C510.2, C511.2, C512.2, C513.2, D502.1 (K), D507.2 (A), Q506.2 (S), R506.2, R510.2, R516.2, R522.2, R524.2, SW501.2, SW502.2, SW503.2, TP504.1, U501.22 (J1-22/G), U501.23 (J3-1/G), U501.43 (J3-21/G), U501.44 (J3-22/G), U504.1 (GND), U505.2 (GND), U506.4 (GND), U507.3 (GND), U508.3 (GND), U515.2 (GND), U516.2 (GND); also elsewhere on the board
I2C_SCL: U501.15 (J1-15/GPIO9); also elsewhere on the board
I2C_SDA: U501.12 (J1-12/GPIO8); also elsewhere on the board
IBUS_RX_3V3: U501.40 (J3-18/GPIO21); also elsewhere on the board
IMU_INT1: U501.6 (J1-6/GPIO6); also elsewhere on the board
ISERVO_SENSE: U501.26 (J3-4/GPIO1); also elsewhere on the board
LED_1_3V3: U501.28 (J3-6/GPIO42); also elsewhere on the board
LED_2_3V3: U501.29 (J3-7/GPIO41); also elsewhere on the board
LED_3_3V3: U501.30 (J3-8/GPIO40); also elsewhere on the board
LED_4_3V3: U501.31 (J3-9/GPIO39); also elsewhere on the board
OUT_LOCK: Q507.3 (D), R524.1, TP506.1; also elsewhere on the board
P3V3_OK: Q506.1 (G), R510.1, U504.2 (~RESET); also elsewhere on the board
SERVO_AUX1_PWM_3V3: U501.10 (J1-10/GPIO17); also elsewhere on the board
SERVO_AUX2_PWM_3V3: U501.20 (J1-20/GPIO14); also elsewhere on the board
SERVO_FRONT_PWM_3V3: U501.8 (J1-8/GPIO15); also elsewhere on the board
SERVO_PWR_EN: U501.7 (J1-7/GPIO7); also elsewhere on the board
SERVO_REAR_PWM_3V3: U501.9 (J1-9/GPIO16); also elsewhere on the board
VSERVO_SENSE: U501.5 (J1-5/GPIO5); also elsewhere on the board

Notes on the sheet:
1 5 V feed and 3.3 V
Carrier +5V -> D501 -> DevKit 5V pin (diode-OR with the DevKit USB diodes, own extension, Versorgung 3.11). +3V3 = DevKit LDO only.
2 Operator and defaults
R501: ACT_OE_N high at reset (buffers Hi-Z). SW501 = latch clock (O-35); GPIO10 via R518 47k, no RC (O-21). D502 LED. R519 1k: ACT_ARMED read-back -> GPIO18 (TP501).
3 DevKit socket U501
Original ESP32-S3-DevKitC-1-N16R8 v1.1; pads 1-22 = J1, 23-44 = J3. Reserved pins: no-connect (pinmap.csv). Signals leave as global labels to the other sheets.
4 VBAT measurement (O-21)
Q505 closes the divider only while P3V3_OK is high; C504 1 nF, D506 holds VBAT_DIV <= +3V3 + 0.24 V. 12.6 V -> 1.80 V.
5 3.3 V supervisor -> P3V3_OK
TLV809E 2.93 V: P3V3_OK high only while +3V3 is good (33-67 ms delay). Drives Q506 here, Q406 (ServoPower) and U602 EN (Lighting_IO).
7 Wiederanlaufsperre (O-35)
U505 clears latch U506 when VBAT_PROT < 9.62-10.40 V or DevKit EN is low (RESET); latch on +3V3. Only a rising Schmitt edge (U507) of the SW501 node arms it; GPIO10 via R518 cannot. CLK/CLR via Schmitt buffers U507/U508. ACT_ARMED -> Q407 (ServoPower), ACT_DISARMED -> U204 (Actuators).
6 Programmierung und Neustart
RESET SW502: EN -> GND (DevKit R5 10k, C6 1 uF). BOOT SW503: GPIO0 -> GND, internal pull-up = SPI boot. Download: hold BOOT, press RESET, release BOOT. RESET is no power switch.
8 Ausgangssperre O-37: rails invalid -> RUN and ESC line clamped, U201 Hi-Z
Controller: DevKit socket, 5 V feed, 3.3 V, defaults and protected measurement inputs (Versorgung 3.11-3.13).
LOCK_SUP 5.0 V from VBAT_PROT (R520, D507) powers both supervisors: no rail is needed to lock. U515: +3V3 < 3.024-3.116 V, U516: +5V < 4.21-4.55 V -> RAILS_OK low (wired AND, R523) -> Q507 on -> OUT_LOCK = LOCK_SUP: Q408 (ServoPower) holds RUN low, Q206 (Actuators) holds ESC_DRV low, U204 (Actuator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
